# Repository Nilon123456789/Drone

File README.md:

# Drone
An open source multi-use drone made with arduino and 3d printing

Features

- Simple to use
- Easily editable
- Versatile

## Libraries

This project uses these following libraries

| Library | GitHub page |
| ------------- | ------------- |
| TinyMPU6050 | https://github.com/gabriel-milan/TinyMPU6050 |
| Servo | https://github.com/arduino-libraries/Servo |

## Require parts
Wearing or 3d printed part may need to be modified to suit other parts

| Part | quantity |
| ------------- | ------------- |
| Arduino nano | 1 |
| MPU 6050 | 1 |
| Pref board | 150x100mm |
| PLA or PETG | ≈ 1 kg |
| Jumper wire | pqt. 10 |
| Break away pins | pqt 25|
| zip ties | pqt 30 |
| M2.5 stand off | 6 |
| M3 nuts | 32 |
| M3x12 bolts | 32 |

## Build instruction
Coming later

## 3D printing instruction 
Coming later

## Programation and Setup
Coming later

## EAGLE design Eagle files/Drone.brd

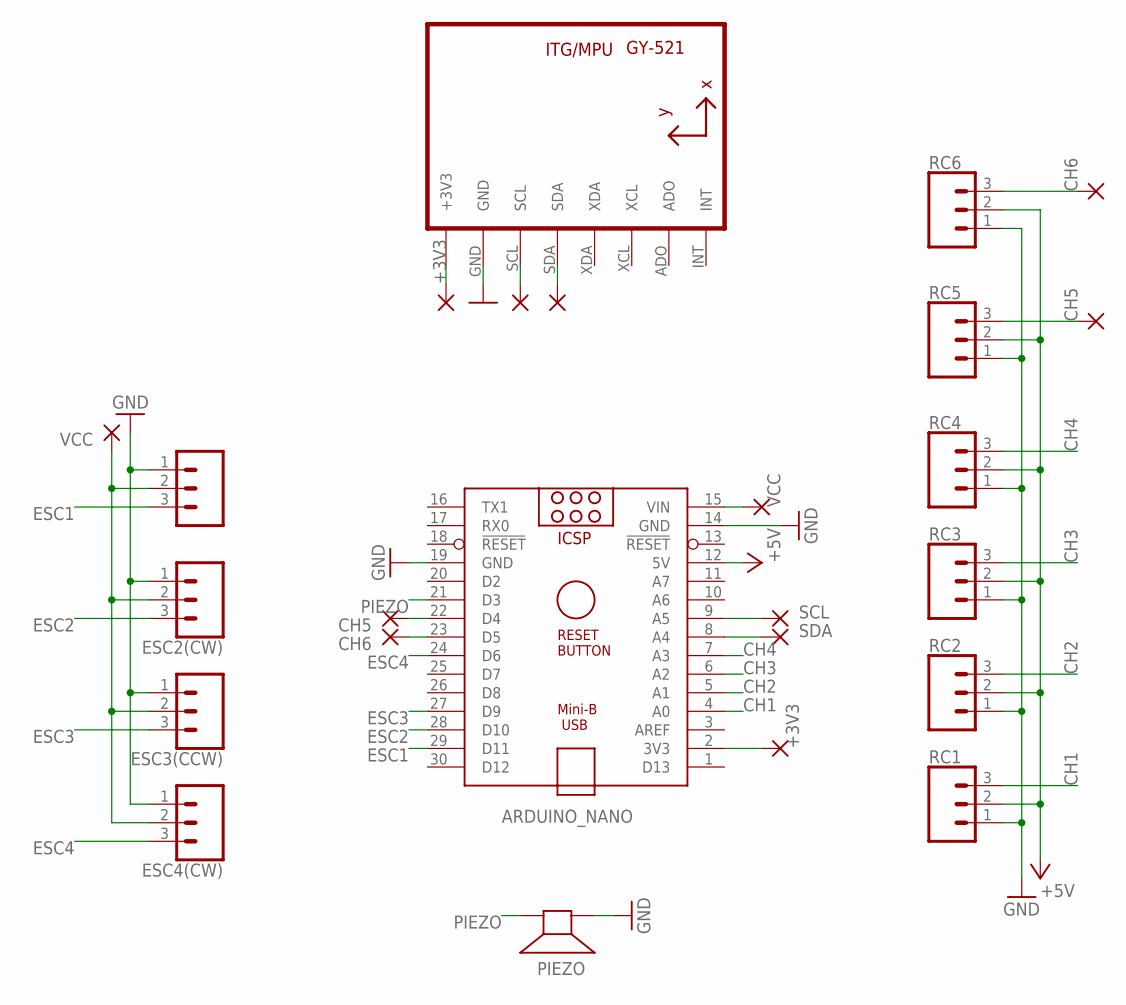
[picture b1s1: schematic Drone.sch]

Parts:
+3V3-1, +3V3-2: +3V3; 1,6/0,8
ARDUINO_NANO: ARDUINO_NANO
CH5, CH5-2, CH6, CH6-2: SCL; 1,6/0,8
ECS1(CCW): CONN_03; 1X03
ESC2(CW), ESC3(CCW), ESC4(CW): CONN_03; 1X03
PIEZO: SPEAKER/AL60P; AL60P
RC1, RC2, RC3, RC4, RC5, RC6: CONN_03; 1X03
SCL: SCL; 1,6/0,8
SCL-2: SCL; 1,6/0,8
SDA: SDA; 1,6/0,8
SDA-2: SDA; 1,6/0,8
U1: GY-521MPU6050; GY-521
VCC-1, VCC-2: VCC; 1,6/0,8

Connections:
+3V3: +3V3-1.1, +3V3-2.1, ARDUINO_NANO.2 (3V3), U1.VCC (+3V3)
+5V: ARDUINO_NANO.12 (5V), RC1.2, RC2.2, RC3.2, RC4.2, RC5.2, RC6.2
CH1: ARDUINO_NANO.4 (A0), RC1.3
CH2: ARDUINO_NANO.5 (A1), RC2.3
CH3: ARDUINO_NANO.6 (A2), RC3.3
CH4: ARDUINO_NANO.7 (A3), RC4.3
CH5: ARDUINO_NANO.22 (D4), CH5.1, CH5-2.1, RC5.3
CH6: ARDUINO_NANO.23 (D5), CH6.1, CH6-2.1, RC6.3
ESC1: ARDUINO_NANO.29 (D11), ECS1(CCW).3
ESC2: ARDUINO_NANO.28 (D10), ESC2(CW).3
ESC3: ARDUINO_NANO.27 (D9), ESC3(CCW).3
ESC4: ARDUINO_NANO.24 (D6), ESC4(CW).3
GND: ARDUINO_NANO.14 (GND), ARDUINO_NANO.19 (GND), ECS1(CCW).1, ESC2(CW).1, ESC3(CCW).1, ESC4(CW).1, PIEZO.1 (+), RC1.1, RC2.1, RC3.1, RC4.1, RC5.1, RC6.1, U1.GND
PIEZO: ARDUINO_NANO.21 (D3), PIEZO.2 (-)
SCL: ARDUINO_NANO.9 (A5), SCL.1, SCL-2.1, U1.SCL
SDA: ARDUINO_NANO.8 (A4), SDA.1, SDA-2.1, U1.SDA
VCC: ARDUINO_NANO.15 (VIN), ECS1(CCW).2, ESC2(CW).2, ESC3(CCW).2, ESC4(CW).2, VCC-1.1, VCC-2.1

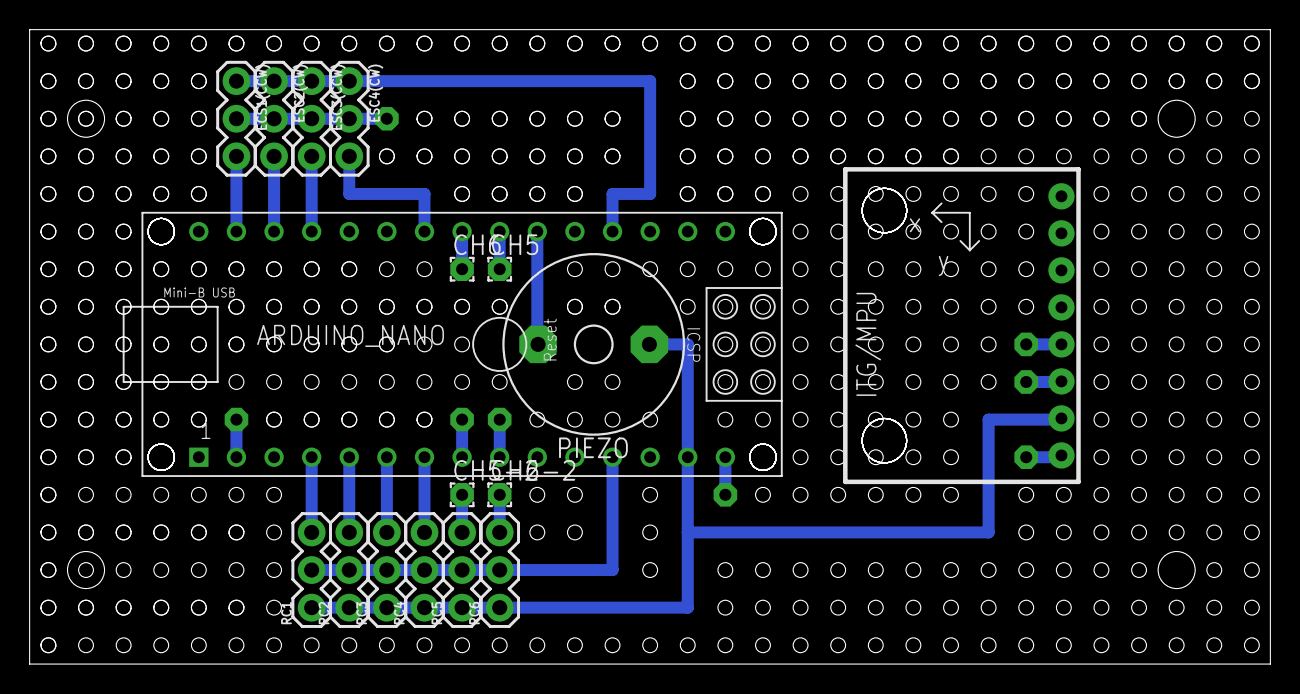
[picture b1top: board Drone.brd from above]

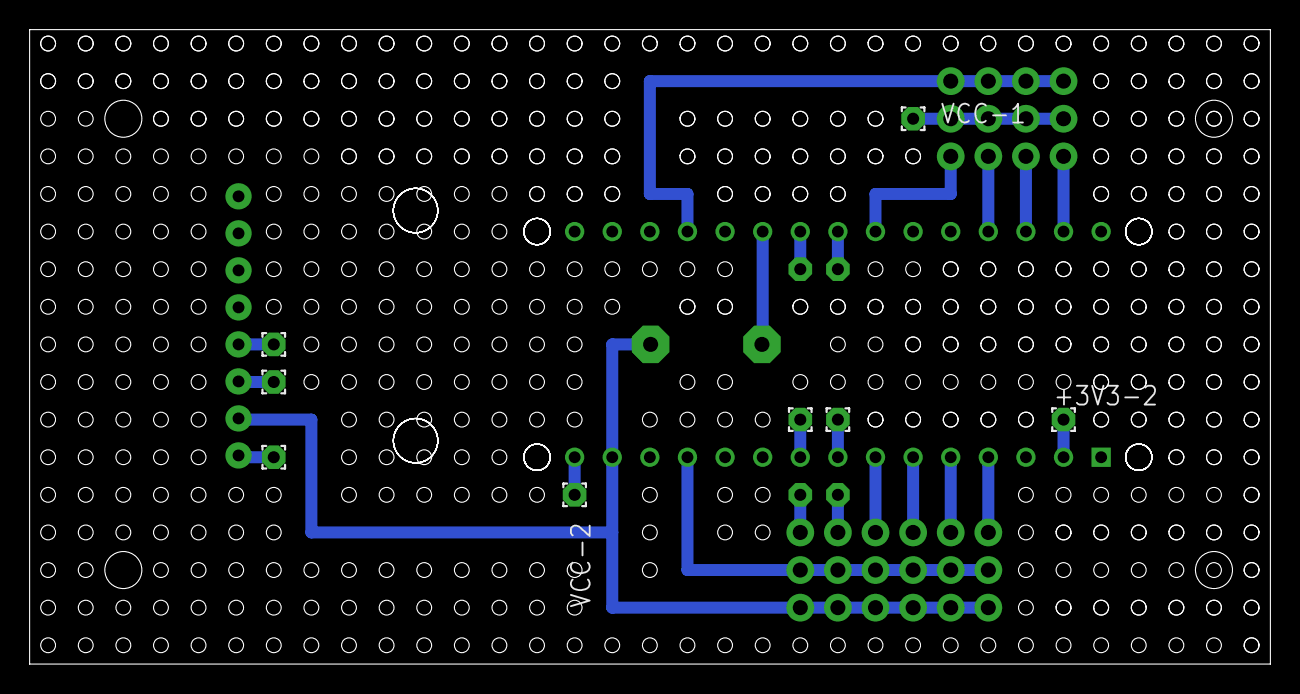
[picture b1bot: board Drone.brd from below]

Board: 2 copper layers, 83.8 x 42.9 mm, 25 parts (8 on the bottom side), 17 nets.

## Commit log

2022-05-30 Purging all DS_Store
2022-05-30 Update .gitignore and push settings
2022-05-31 Adding new test scripts
2022-05-31 New version of the Drone main script
2022-05-31 Adding the F3d files and stl files
2022-06-10 Adding Board schematic & updating gitignore for eagle files
2022-06-10 Update Control_Test.ino
    Adding mapping option for the mpu axis to adapte form diferent mpu positions
2022-06-10 Update RC_Test.ino & Setup.ino
    Adding support for two extra input
2022-06-10 Updated Config.h and Drone.ino
    Adding Alarm sound if second input is switched
    Adding Arming switch
    Adding mapping for the mpu
    Adding booting sound
    Refactoring a bit of code
2022-06-11 Updated the Drone board files
2022-06-11 Create LICENSE
2022-06-20 Patching arming if
    The armed if was not continuing if the drone was armed due to the default else return statement
2022-06-20 Cleaning up a bit the Drone.ino file
    Moved the call to get the MPU6050 angles to a separate void
2022-06-20 Added seting to tune the power of individual ESC
    Added the escTuner variable to help equalize the strength of the ESC
2022-06-21 Adding an alarm and motor cutoff if drone is upside down

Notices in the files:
parts and their libraries:
SparkFun-Connectors: Licensing: Creative Commons ShareAlike 4.0 International - https://creativecommons.org/licenses/by-sa/4.0
